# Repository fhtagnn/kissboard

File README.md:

# kissboard
Hardware and Firmware for the Kissboard keyboard concept by urac/wolf (AdNW user community).

Layout explanation
* Middle label: standard tap output
* Bottom Label: double tap output
* Top Label: hold modifier
* Corner labels: Layers

## The idea
The physical key layout is inspired by a 2012 discussion on the german [neo user mailinglist](http://narkive.com/9UhJnT14) about custom keyboards using the [AdNW layout](http://www.adnw.de/). Specifically user urac proposed a minimalistic approach (KISS=keep it stupid simple) simply named [kissboard](https://docs.google.com/document/d/1TQ_BZYoZRW-ZFIaiolPAr9yNul6SBKypeA4ataw5Tz4/edit). Later, AdNW user wolf build a handwired custom board using a modified AdNW variant called PUQ discussed [here](https://groups.google.com/forum/#!topic/adnw/NdMOlERoFa4).

## PCB design
The PCB design was inspired by the [Mitosis Project](https://imgur.com/a/mwTFj) and its [Mitosis hardware](https://github.com/reversebias/mitosis-hardware) created by [reversebias](https://github.com/reversebias). Software implementation is a slightly modified copy of the [Mitosis Firmware](https://github.com/reversebias/mitosis) using [QMK](https://github.com/qmk/qmk_firmware/tree/master/keyboards/mitosis). The original Mitosis design is only available as an altium designer project. I used the freely available [KiCad](http://kicad.org/) and the converter [altium2kicad](https://github.com/thesourcerer8/altium2kicad) to first convert the layout to kicad, then create footprints of all important components and rebuild the design according to the kissboard/wolf switch layout.

## Firmware
The [Kissboard firmware](https://github.com/fhtagnn/mitosis) is a fork of the [Original Mitosis firmware](https://github.com/reversebias/mitosis) modified to reflect the pin connections used in this layout. Also, I use a [QMK Fork](https://github.com/fhtagnn/qmk_firmware) to implement any changes in the layout.

## Build Log
[Incomplete build log](https://imgur.com/a/pN4dOZB "Imgur Album")

# How to build
## Hardware
Source materials using the information in the BOM folder. Wait...build! :D

## Software
QMK can be build via Docker (below windows call) or per QMK instructions

```docker run -e keymap=default -e keyboard=ergodox_ez --rm -v PATHtoQMK:/qmk:rw edasque/qmk_firmware```

Firmware can be build via Docker (below windows call) or using any arm-gcc build environment. Follow instructions in firmware folder.

```docker run -it -v PATHtoFIRMWARE:/work/kissboard/:rw fhtagnn/kissboard_firmware```

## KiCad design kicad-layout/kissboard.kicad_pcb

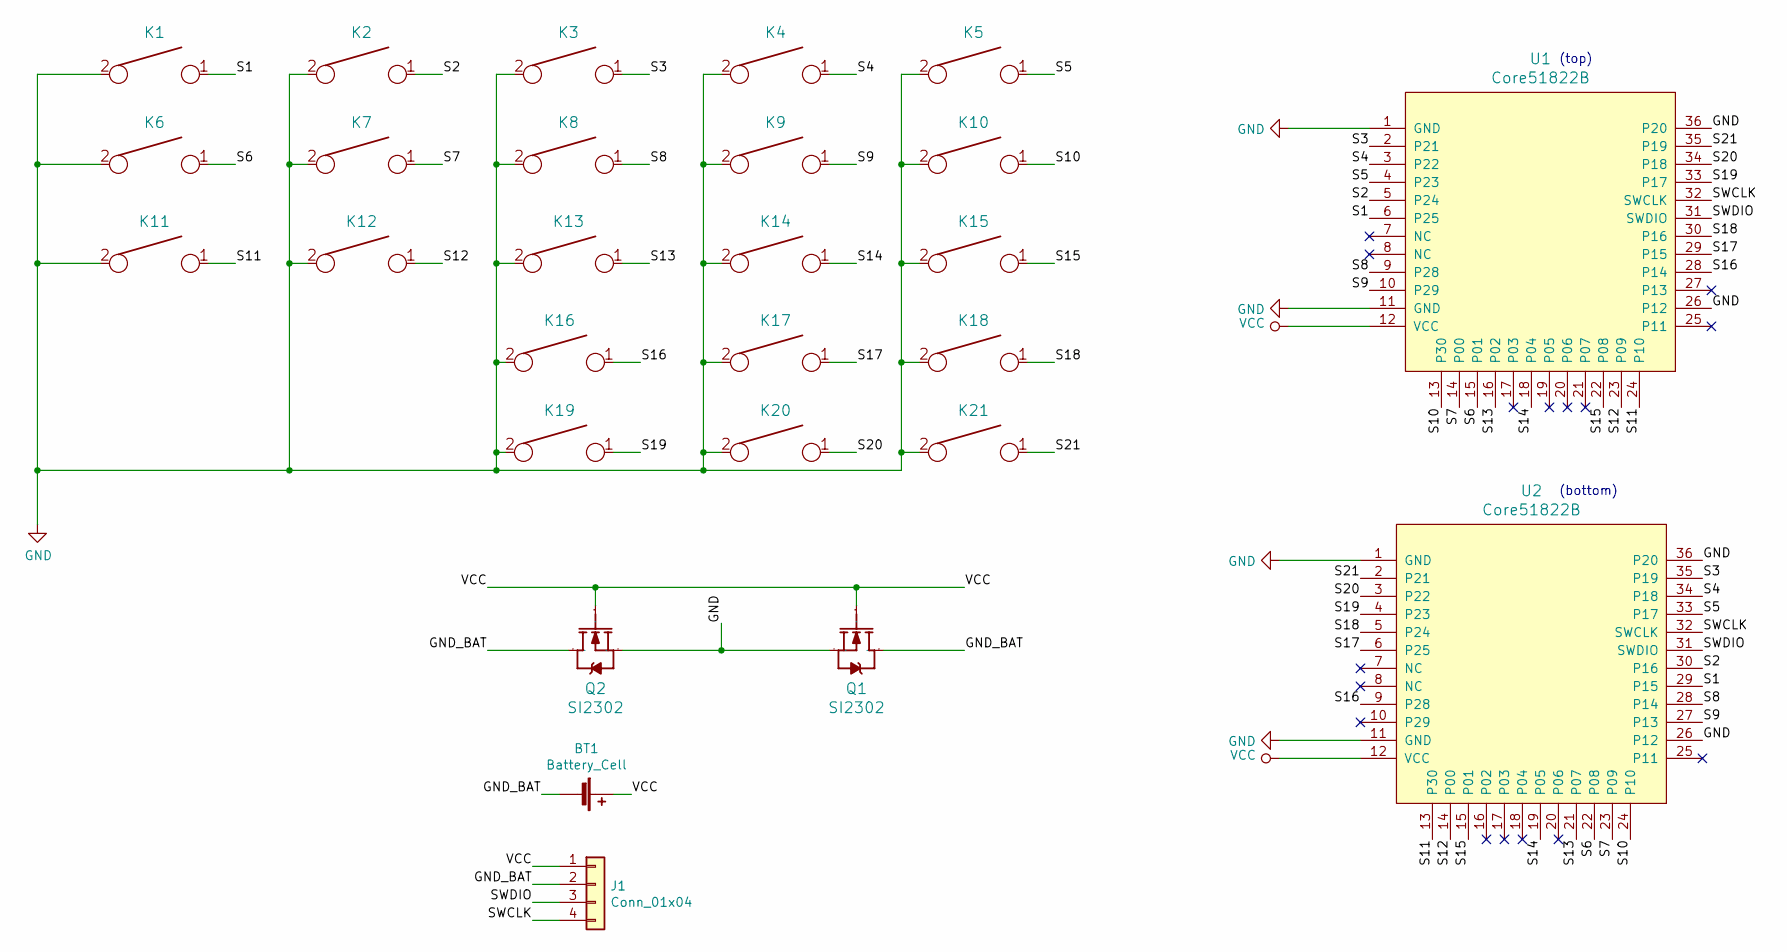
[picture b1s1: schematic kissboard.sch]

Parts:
BT1: Battery_Cell; battery_contacts
J1: Conn_01x04; programming_port
K1, K2, K3, K4, K5, K6, K7, K8, K9, K10, K11, K12, K13, K14, K15, K16, K17, K18, K19, K20, K21: KEYSW; cherry
Q1, Q2: SI2302; SI3202CDS
U1, U2: Core51822B; Core51822(B)

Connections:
/GND_BAT: BT1.2 (-), J1.2, Q1.3 (D), Q2.3 (D)
/S1: K1.1, U1.6 (P25), U2.29 (P15)
/S2: K2.1, U1.5 (P24), U2.30 (P16)
/S3: K3.1, U1.2 (P21), U2.35 (P19)
/S4: K4.1, U1.3 (P22), U2.34 (P18)
/S5: K5.1, U1.4 (P23), U2.33 (P17)
/S6: K6.1, U1.15 (P01), U2.22 (P08)
/S7: K7.1, U1.14 (P00), U2.23 (P09)
/S8: K8.1, U1.9 (P28), U2.28 (P14)
/S9: K9.1, U1.10 (P29), U2.27 (P13)
/S10: K10.1, U1.13 (P30), U2.24 (P10)
/S11: K11.1, U1.24 (P10), U2.13 (P30)
/S12: K12.1, U1.23 (P09), U2.14 (P00)
/S13: K13.1, U1.16 (P02), U2.21 (P07)
/S14: K14.1, U1.18 (P04), U2.19 (P05)
/S15: K15.1, U1.22 (P08), U2.15 (P01)
/S16: K16.1, U1.28 (P14), U2.9 (P28)
/S17: K17.1, U1.29 (P15), U2.6 (P25)
/S18: K18.1, U1.30 (P16), U2.5 (P24)
/S19: K19.1, U1.33 (P17), U2.4 (P23)
/S20: K20.1, U1.34 (P18), U2.3 (P22)
/S21: K21.1, U1.35 (P19), U2.2 (P21)
/SWCLK: J1.4, U1.32 (SWCLK), U2.32 (SWCLK)
/SWDIO: J1.3, U1.31 (SWDIO), U2.31 (SWDIO)
GND: K1.2, K2.2, K3.2, K4.2, K5.2, K6.2, K7.2, K8.2, K9.2, K10.2, K11.2, K12.2, K13.2, K14.2, K15.2, K16.2, K17.2, K18.2, K19.2, K20.2, K21.2, Q1.2 (S), Q2.2 (S), U1.1 (GND), U1.11 (GND), U1.26 (P12), U1.36 (P20), U2.1 (GND), U2.11 (GND), U2.26 (P12), U2.36 (P20)
VCC: BT1.1 (+), J1.1, Q1.1 (G), Q2.1 (G), U1.12 (VCC), U2.12 (VCC)

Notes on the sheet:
(bottom)
(top)

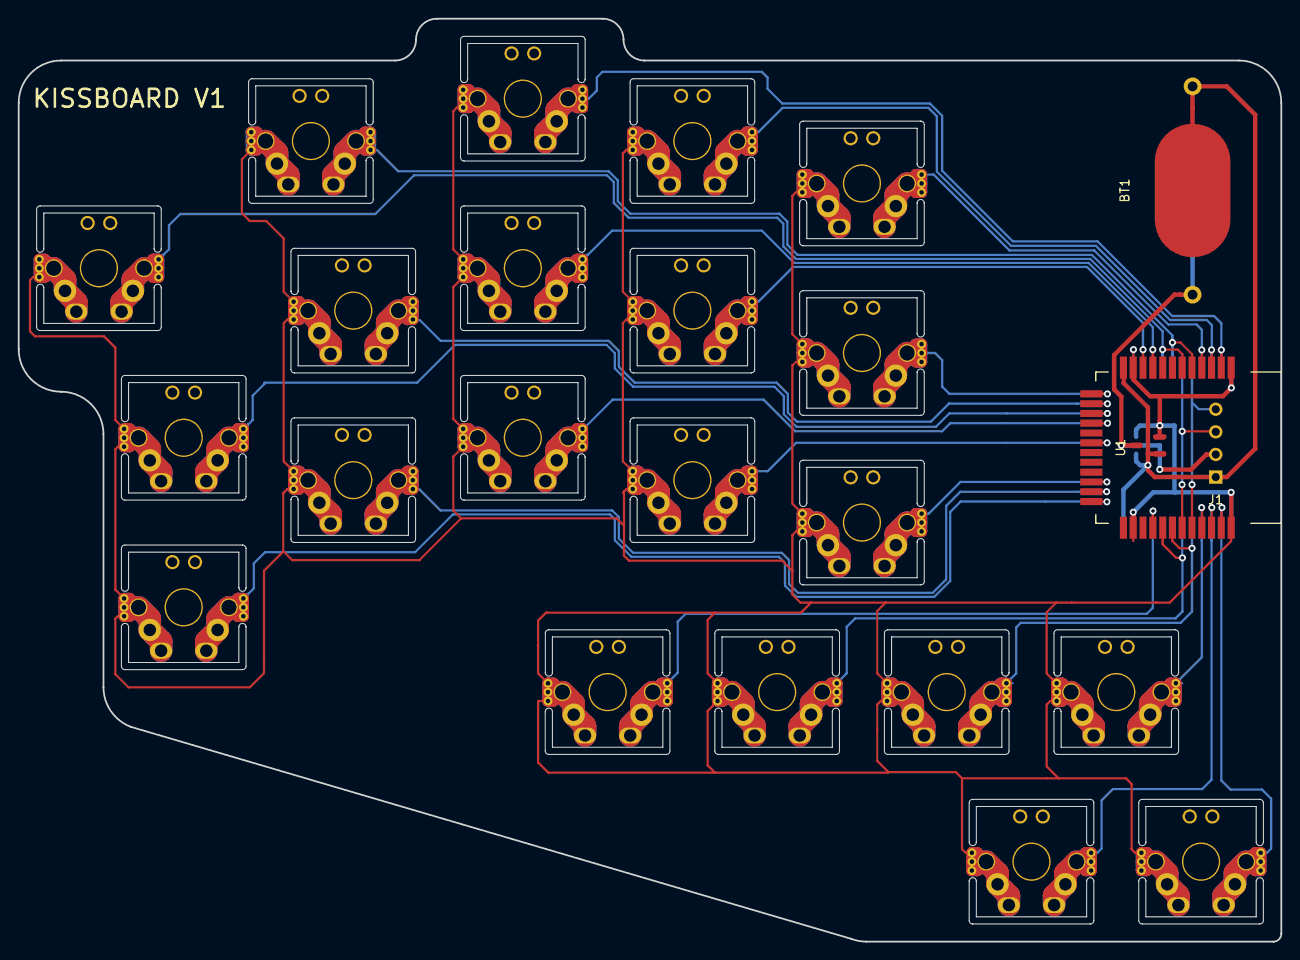
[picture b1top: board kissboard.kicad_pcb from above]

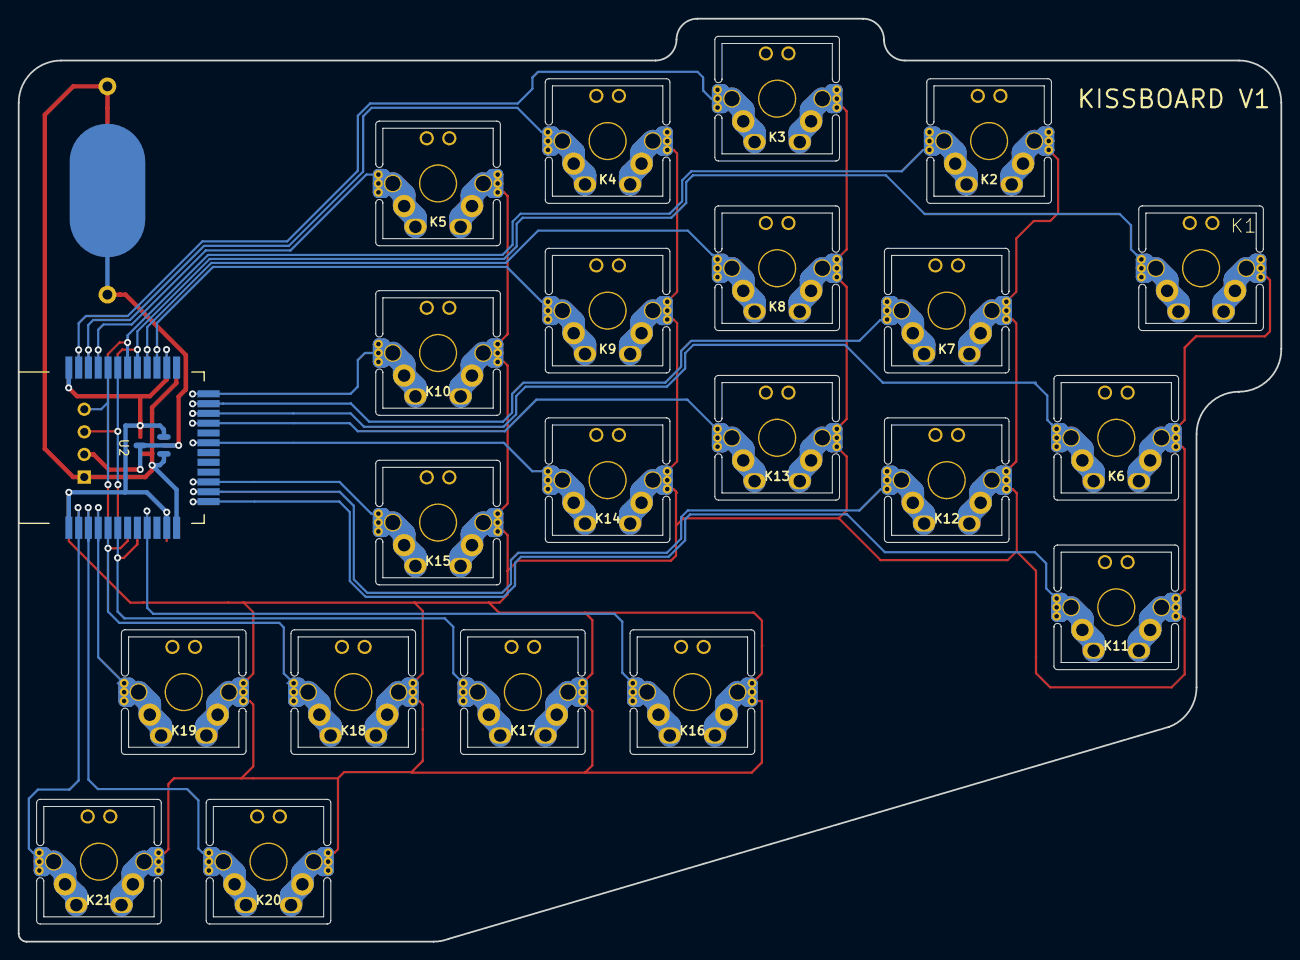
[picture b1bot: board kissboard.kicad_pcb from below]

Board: 2 copper layers, 141.9 x 103.7 mm, 27 parts (2 on the bottom side), 26 nets.

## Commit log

2018-04-05 intial commit of kissboard kicad files and readme
2018-04-05 readme update with inital information
2018-04-05 Updated readme.md with furter infos
    Added links to forked firmware and QMK repos
2018-04-05 Reshaping of PCB. Cleaning of old tracks in the works...
2018-04-06 Update README.md
    fix typo
2018-04-07 Completed cleaning of tracks for new placement and added updated pictures.
2018-04-08 traces complete, all files updated, gerber.zip added
2018-04-08 Adjusted edge cut, updated pictures and pdf prints
2018-04-08 Updated gerber files and added zip file
2018-04-08 Added missing files
2018-04-18 Fixed wrong connection of S16 on the bottom layer
2018-04-19 Added Dockerfile for Windows build environment
2018-04-19 Copied mitosis firmware fork into the kissboard repository
2018-04-19 Fixed docker repository name
2018-04-19 More minor readme fixes in firmware part
2018-04-24 added bill of materials
2018-06-05 Layout adjusted: lower pinky finger column and straight thumb row
2018-06-05 tiny adjustment of a single track
2018-06-10 Fixed thumb row: moved half key in towards thumb
2018-08-16 Added precompiled hex files for left and right half.
2018-08-29 Added Pictures to readme.md
2018-08-29 Added img titles and log link to readme
2018-08-29 Corrected pin/key assigment to match expected key places for QMK
2018-10-30 corrected typo in the pin assignement. Left key 16 was not assigned, but key 19 twice.
2018-10-30 First commit for the kisscase files.
2021-11-09 Update README.md
    https://forum.kicad.info/t/warning-avoid-all-links-to-kicad-pcb-org-use-kicad-org/31521
